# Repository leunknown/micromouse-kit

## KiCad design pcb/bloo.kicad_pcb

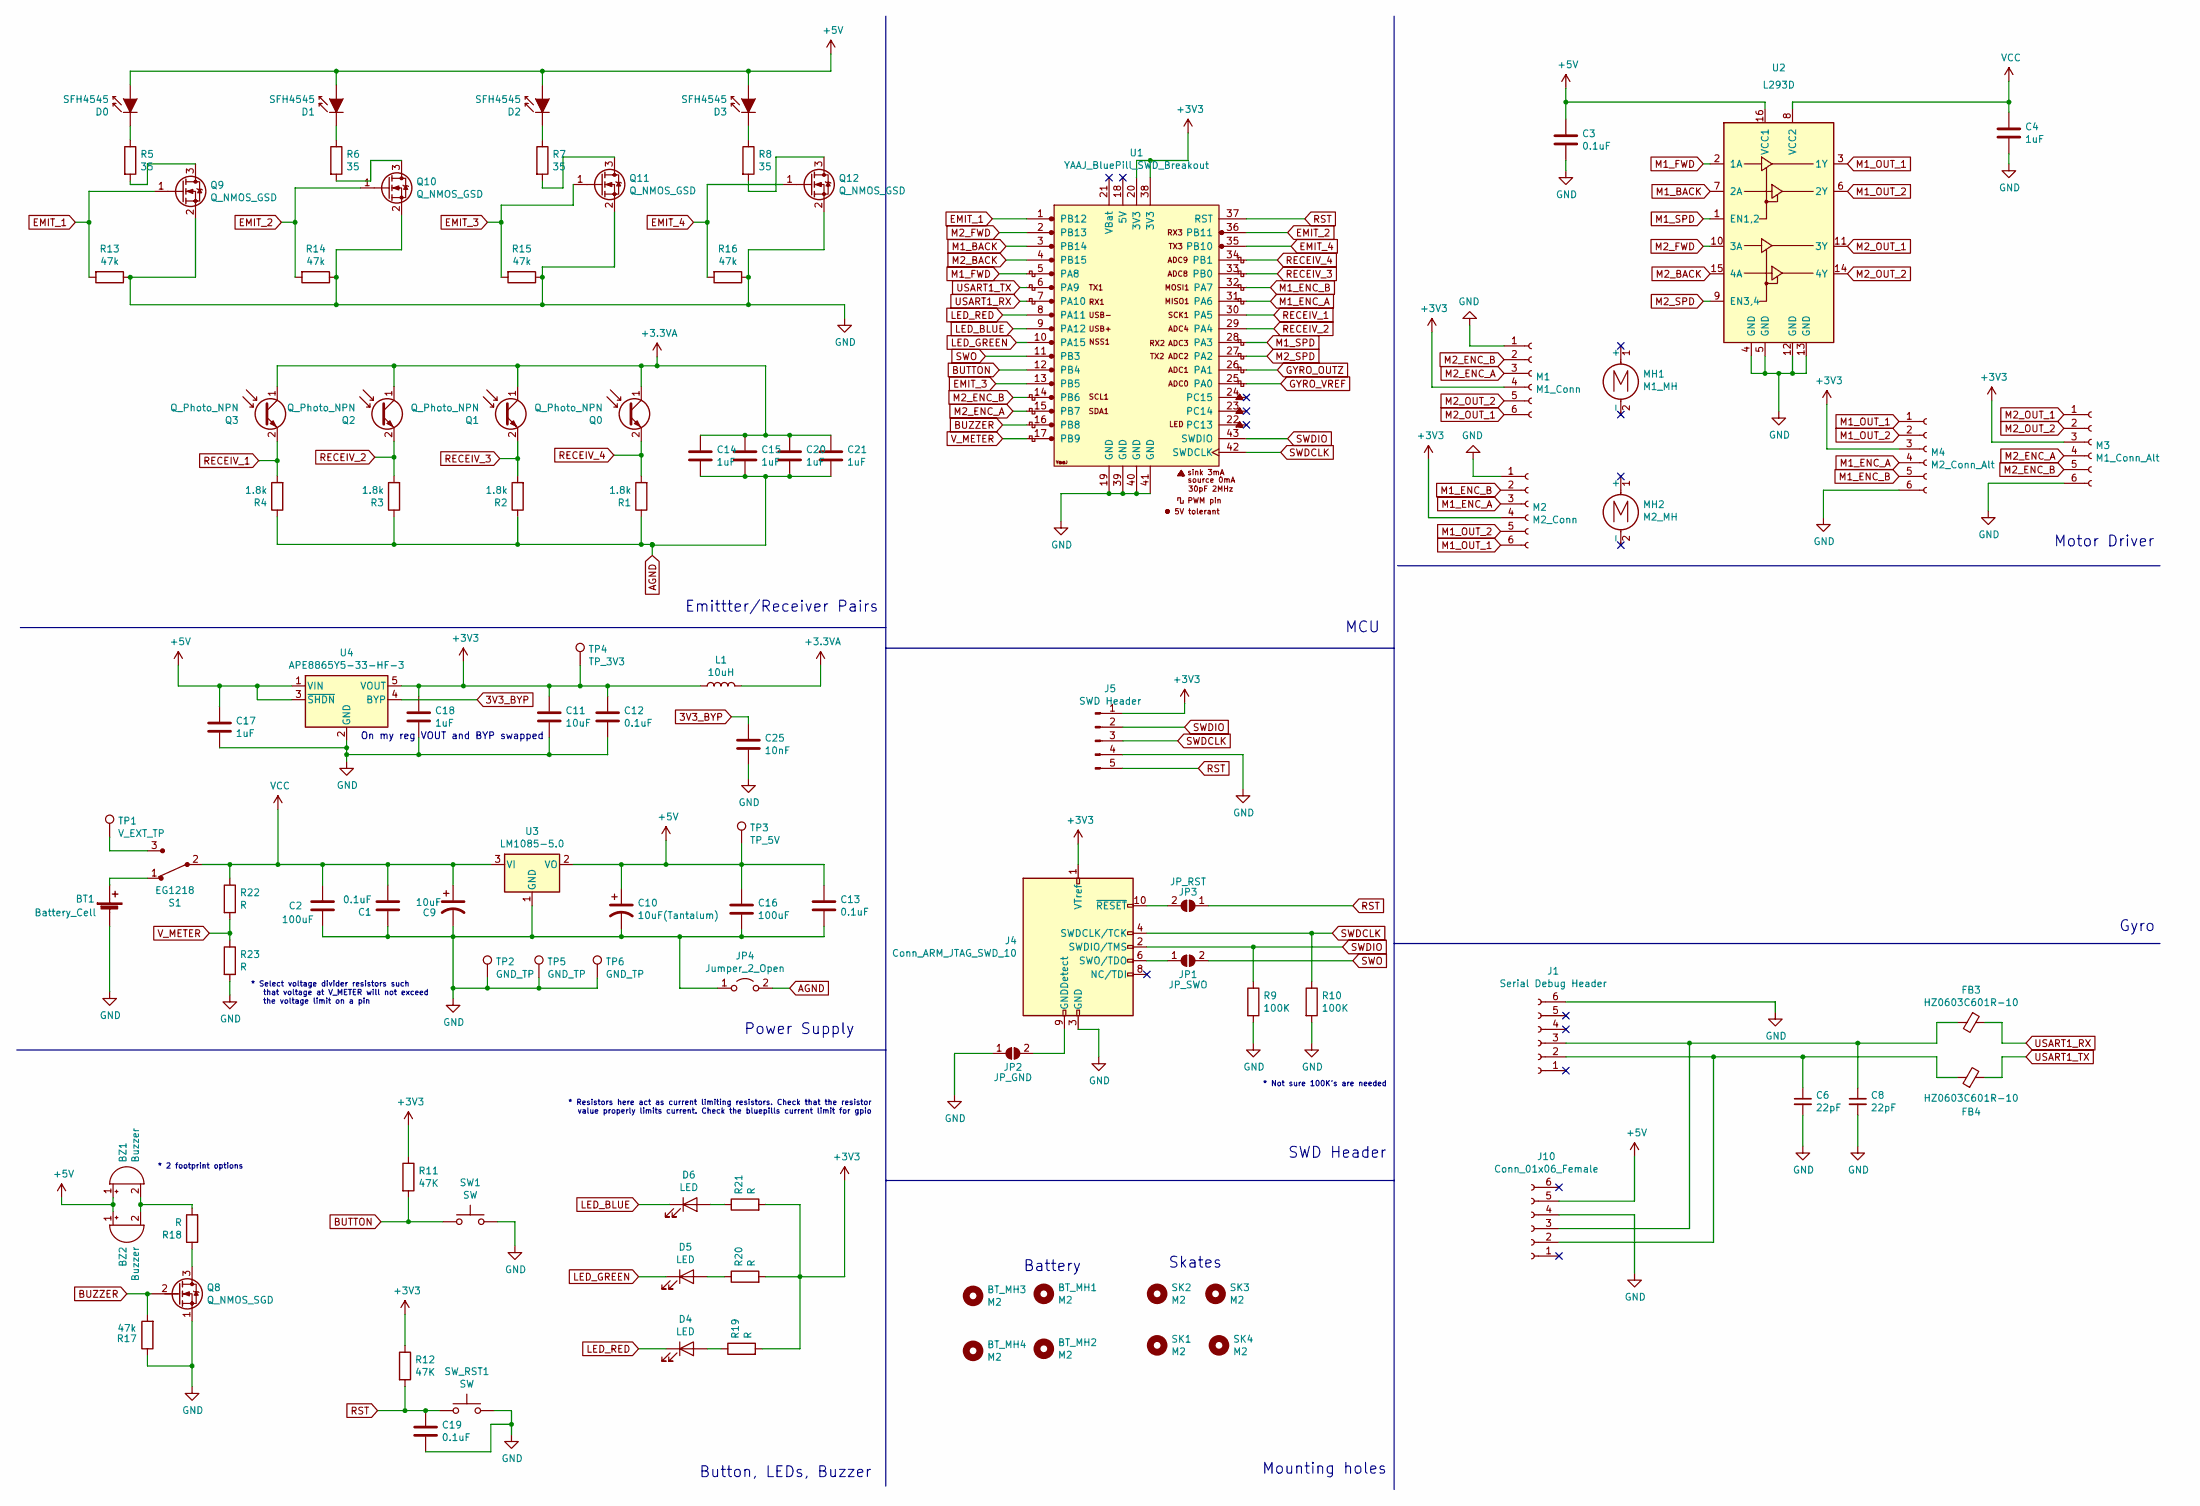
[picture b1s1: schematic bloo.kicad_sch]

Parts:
BT1: Battery_Cell; PinSocket_1x02_P2.54mm_Vertical
BT_MH1, BT_MH2, BT_MH3, BT_MH4: M2; MountingHole_2.2mm_M2
BZ1: Buzzer; Buzzer_12x9.5RM7.6
BZ2: Buzzer; Buzzer_TDK_PS1240P02BT_D12.2mm_H6.5mm
C1, C3, C12, C13, C19: 0.1uF; C_1206_3216Metric_Pad1.33x1.80mm_HandSolder
C2, C16: 100uF; CP_Radial_D6.3mm_P2.50mm
C4, C14, C15, C17, C18, C20, C21: 1uF; C_1206_3216Metric_Pad1.33x1.80mm_HandSolder
C6, C8: 22pF; C_0603_1608Metric_Pad1.08x0.95mm_HandSolder
C9, C11: 10uF; C_1206_3216Metric_Pad1.33x1.80mm_HandSolder
C10: 10uF(Tantalum); C_1206_3216Metric_Pad1.33x1.80mm_HandSolder
C25: 10nF; C_1206_3216Metric_Pad1.33x1.80mm_HandSolder
D0, D1, D2, D3: SFH4545; Emitter
D4, D5, D6: LED; LED_0805_2012Metric_Pad1.15x1.40mm_HandSolder
FB3, FB4: HZ0603C601R-10; R_0603_1608Metric_Pad0.98x0.95mm_HandSolder
J1: Serial Debug Header; PinHeader_1x06_P2.54mm_Vertical
J4: Conn_ARM_JTAG_SWD_10; PinHeader_2x05_P1.27mm_Vertical
J5: SWD Header; PinHeader_1x05_P2.54mm_Vertical
J10: Conn_01x06_Female; PinSocket_1x06_P2.54mm_Vertical
JP1: JP_SWO; SolderJumper-2_P1.3mm_Open_Pad1.0x1.5mm
JP2: JP_GND; SolderJumper-2_P1.3mm_Open_Pad1.0x1.5mm
JP3: JP_RST; SolderJumper-2_P1.3mm_Open_Pad1.0x1.5mm
JP4: Jumper_2_Open; SolderJumper-2_P1.3mm_Bridged_Pad1.0x1.5mm
L1: 10uH; L_1206_3216Metric_Pad1.42x1.75mm_HandSolder
M1: M1_Conn; JST_SH_BM06B-SRSS-TB_1x06-1MP_P1.00mm_Vertical
M2: M2_Conn; JST_SH_BM06B-SRSS-TB_1x06-1MP_P1.00mm_Vertical
M3: M1_Conn_Alt; PinHeader_1x06_P2.54mm_Vertical
M4: M2_Conn_Alt; PinHeader_1x06_P2.54mm_Vertical
MH1: M1_MH; Motor_mouse
MH2: M2_MH; Motor_mouse
Q0, Q1, Q2, Q3: Q_Photo_NPN; Emitter
Q8: Q_NMOS_SGD; SOT-23
Q9, Q10, Q11, Q12: Q_NMOS_GSD; SOT-23
R1, R2, R3, R4: 1.8k; R_1206_3216Metric_Pad1.30x1.75mm_HandSolder
R5, R6, R7, R8: 35; R_1206_3216Metric_Pad1.30x1.75mm_HandSolder
R9, R10: 100K; R_1206_3216Metric_Pad1.30x1.75mm_HandSolder
R11, R12: 47K; R_1206_3216Metric_Pad1.30x1.75mm_HandSolder
R13, R14, R15, R16, R17: 47k; R_1206_3216Metric_Pad1.30x1.75mm_HandSolder
R18, R19, R20, R21, R22, R23: R; R_1206_3216Metric_Pad1.30x1.75mm_HandSolder
S1: EG1218; 1103M2S4CQE2; MPN EG1218; Digi-Key_PN EG1903-ND
SK1, SK2, SK3, SK4: M2; MountingHole_2.2mm_M2
SW1: SW; SW_SPST_REED_CT05-XXXX-G1
SW_RST1: SW; SW_SPST_REED_CT05-XXXX-G1
TP1: V_EXT_TP; PinHeader_1x01_P2.54mm_Vertical
TP2, TP5, TP6: GND_TP; PinHeader_1x01_P2.54mm_Vertical
TP3: TP_5V; PinHeader_1x01_P2.54mm_Vertical
TP4: TP_3V3; PinHeader_1x01_P2.54mm_Vertical
U1: YAAJ_BluePill_SWD_Breakout; YAAJ_BluePill_SWD_2
U2: L293D; DIP-16_W7.62mm
U3: LM1085-5.0; VREG_TO-263-3_TabPin2
U4: APE8865Y5-33-HF-3; SOT-23-5

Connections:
3V3_BYP: C25.1, U4.4 (BYP)
+3.3VA: C14.1, C15.1, C20.1, C21.1, L1.2, Q0.1 (C), Q1.1 (C), Q2.1 (C), Q3.1 (C)
+3V3: C11.1, C12.1, C18.1, J4.1 (VTref), J5.1, L1.1, M1.4, M2.4, M3.3, M4.3, R11.1, R12.1, R19.2, R20.2, R21.2, TP4.1, U1.20 (3V3), U1.38 (3V3), U4.5 (VOUT); also elsewhere on the board
+5V: BZ1.1 (-), BZ2.1 (-), C3.1, C10.1, C13.1, C16.1, C17.1, D0.2 (A), D1.2 (A), D2.2 (A), D3.2 (A), J10.5, TP3.1, U2.16 (VCC1), U3.2 (VO), U4.1 (VIN), U4.3 (~SHDN); also elsewhere on the board
AGND: C14.2, C15.2, C20.2, C21.2, JP4.2 (B), R1.1, R2.1, R3.1, R4.1
BUTTON: R11.2, SW1.1, U1.12 (PB4)
BUZZER: Q8.2 (G), R17.2, U1.16 (PB8)
EMIT_1: Q9.1 (G), R13.2, U1.1 (PB12)
EMIT_2: Q10.1 (G), R14.2, U1.36 (PB11)
EMIT_3: Q11.1 (G), R15.2, U1.13 (PB5)
EMIT_4: Q12.1 (G), R16.2, U1.35 (PB10)
GND: BT1.2 (-), C1.1, C2.2, C3.2, C4.2, C6.2, C8.2, C9.2, C10.2, C11.2, C12.2, C13.2, C16.2, C17.2, C18.2, C19.2, C25.2, J1.6, J4.3 (GND), J4.5 (GND), J5.4, J10.4, JP2.1 (A), JP4.1 (A), M1.1, M2.1, M3.6, M4.6, Q8.1 (S), Q9.2 (S), Q10.2 (S), Q11.2 (S), Q12.2 (S), R9.2, R10.2, R13.1, R14.1, R15.1, R16.1, R17.1, R23.2, SW1.2, SW_RST1.2, TP2.1, TP5.1, TP6.1, U1.19 (GND), U1.39 (GND), U1.40 (GND), U1.41 (GND), U2.4 (GND), U2.5 (GND), U2.12 (GND), U2.13 (GND), U3.1 (GND), U4.2 (GND); also elsewhere on the board
GYRO_OUTZ: U1.26 (PA1)
GYRO_VREF: U1.25 (PA0)
LED_BLUE: D6.1 (K), U1.9 (PA12)
LED_GREEN: D5.1 (K), U1.10 (PA15)
LED_RED: D4.1 (K), U1.8 (PA11)
M1_BACK: U1.3 (PB14), U2.7 (2A)
M1_ENC_A: M2.3, M4.4, U1.31 (PA6)
M1_ENC_B: M2.2, M4.5, U1.32 (PA7)
M1_FWD: U1.5 (PA8), U2.2 (1A)
M1_OUT_1: M2.6, M4.1, U2.3 (1Y)
M1_OUT_2: M2.5, M4.2, U2.6 (2Y)
M1_SPD: U1.28 (PA3), U2.1 (EN1,2)
M2_BACK: U1.4 (PB15), U2.15 (4A)
M2_ENC_A: M1.3, M3.4, U1.15 (PB7)
M2_ENC_B: M1.2, M3.5, U1.14 (PB6)
M2_FWD: U1.2 (PB13), U2.10 (3A)
M2_OUT_1: M1.6, M3.1, U2.11 (3Y)
M2_OUT_2: M1.5, M3.2, U2.14 (4Y)
M2_SPD: U1.27 (PA2), U2.9 (EN3,4)
unnamed: BT1.1 (+), S1.1
unnamed: BZ1.2 (+), BZ2.2 (+), R18.2
unnamed 34: C6.1, FB4.1, J1.2, J10.2; also elsewhere on the board
unnamed 35: C8.1, FB3.2, J1.3, J10.3; also elsewhere on the board
unnamed: D0.1 (K), R5.1
unnamed: D1.1 (K), R6.1
unnamed: D2.1 (K), R7.1
unnamed: D3.1 (K), R8.1
unnamed: D4.2 (A), R19.1
unnamed: D5.2 (A), R20.1
unnamed: D6.2 (A), R21.1
unnamed: J4.6 (SWO/TDO), JP1.1 (A)
unnamed: J4.9 (GNDDetect), JP2.2 (B)
unnamed: J4.10 (~RESET), JP3.2 (B)
unnamed: Q8.3 (D), R18.1
unnamed: Q9.3 (D), R5.2
unnamed: Q10.3 (D), R6.2
unnamed: Q11.3 (D), R7.2
unnamed: Q12.3 (D), R8.2
unnamed: S1.3, TP1.1
RECEIV_1: Q3.2 (E), R4.2, U1.30 (PA5)
RECEIV_2: Q2.2 (E), R3.2, U1.29 (PA4)
RECEIV_3: Q1.2 (E), R2.2, U1.33 (PB0)
RECEIV_4: Q0.2 (E), R1.2, U1.34 (PB1)
RST: C19.1, J5.5, JP3.1 (A), R12.2, SW_RST1.1, U1.37 (RST); also elsewhere on the board
SWDCLK: J4.4 (SWDCLK/TCK), J5.3, R10.1, U1.42 (SWDCLK)
SWDIO: J4.2 (SWDIO/TMS), J5.2, R9.1, U1.43 (SWDIO)
SWO: JP1.2 (B), U1.11 (PB3)
USART1_RX: FB3.1, U1.7 (PA10)
USART1_TX: FB4.2, U1.6 (PA9)
VCC: C1.2, C2.1, C4.1, C9.1, R22.1, S1.2, U2.8 (VCC2), U3.3 (VI)
V_METER: R22.2, R23.1, U1.17 (PB9)

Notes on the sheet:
Mounting holes
Battery
* 2 footprint options
Motor Driver
* Not sure 100K’s are needed
On my reg VOUT and BYP swapped
Emittter/Receiver Pairs
* Resistors here act as current limiting resistors. Check that the resistor value properly limits current. Check the bluepills current limit for gpio
MCU
SWD Header
* Select voltage divider resistors such that voltage at V_METER will not exceed the voltage limit on a pin
Gyro
Button, LEDs, Buzzer
Skates
Power Supply

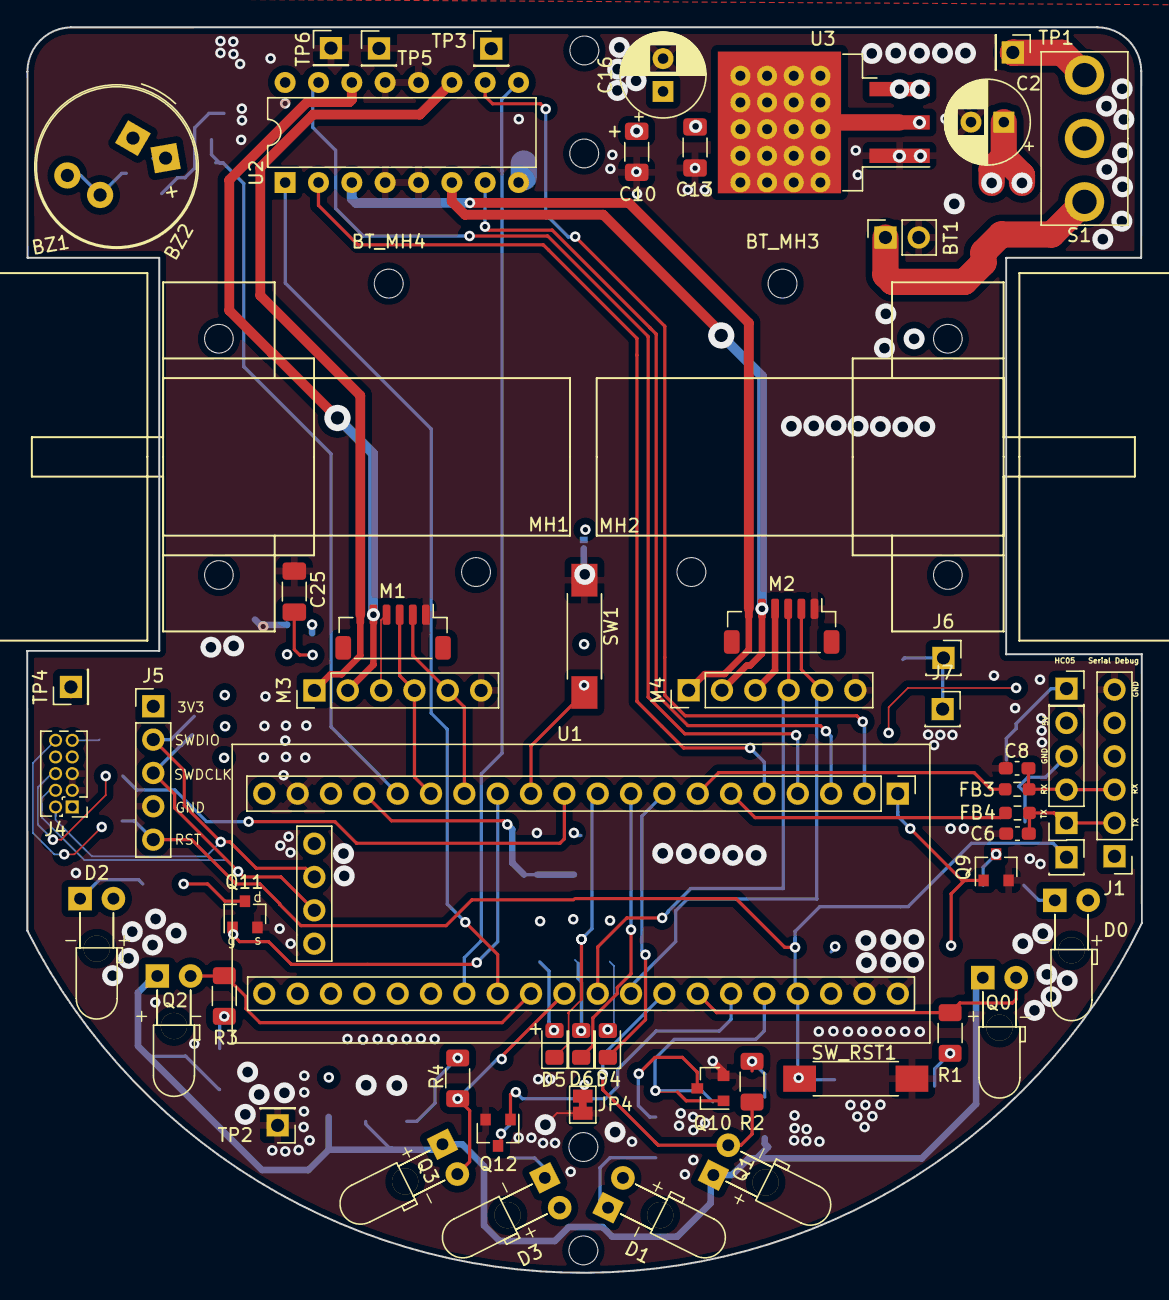
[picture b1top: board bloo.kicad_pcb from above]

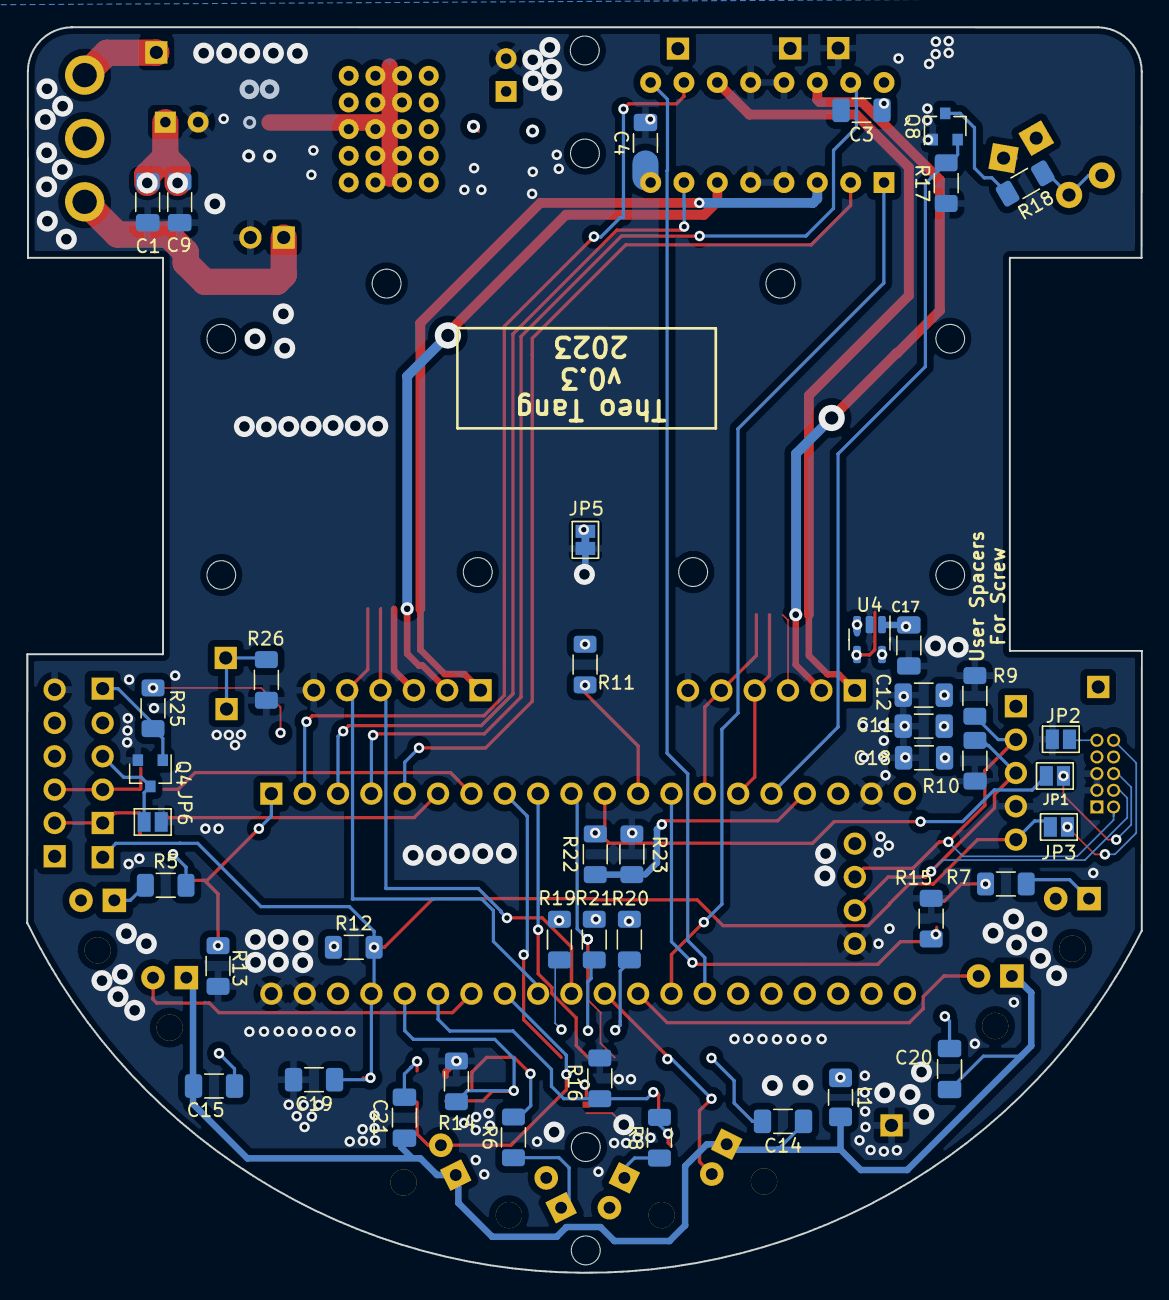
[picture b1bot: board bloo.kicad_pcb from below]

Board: 4 copper layers, 84.9 x 94.9 mm, 109 parts (43 on the bottom side), 64 nets.

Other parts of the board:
J2: Conn_RST; PinSocket_1x01_P2.54mm_Vertical
J3: BLE_PWR; PinSocket_1x01_P2.54mm_Vertical
J6, J7: BOOT0; PinSocket_1x01_P2.54mm_Vertical
J8: Conn_01x04_Female; PinSocket_1x04_P2.54mm_Vertical
JP5: Jumper_2_Open; SolderJumper-2_P1.3mm_Bridged_Pad1.0x1.5mm
JP6: Jumper_2_Open; SolderJumper-2_P1.3mm_Open_Pad1.0x1.5mm
Q4: Q_NMOS_GSD; SOT-23
R25, R26: 47k; R_1206_3216Metric_Pad1.30x1.75mm_HandSolder

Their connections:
+3V3: R25.1; also elsewhere on the board
+5V: J8.4; also elsewhere on the board
GND: JP5.1, JP6.2, Q4.2, R26.1; also elsewhere on the board
unnamed 34: J8.1; also elsewhere on the board
unnamed 35: J8.2; also elsewhere on the board
unnamed: J3.1, Q4.1, R25.2
unnamed: J6.1, J7.1, R26.2
unnamed: J8.3, JP6.1, Q4.3
RST: J2.1; also elsewhere on the board

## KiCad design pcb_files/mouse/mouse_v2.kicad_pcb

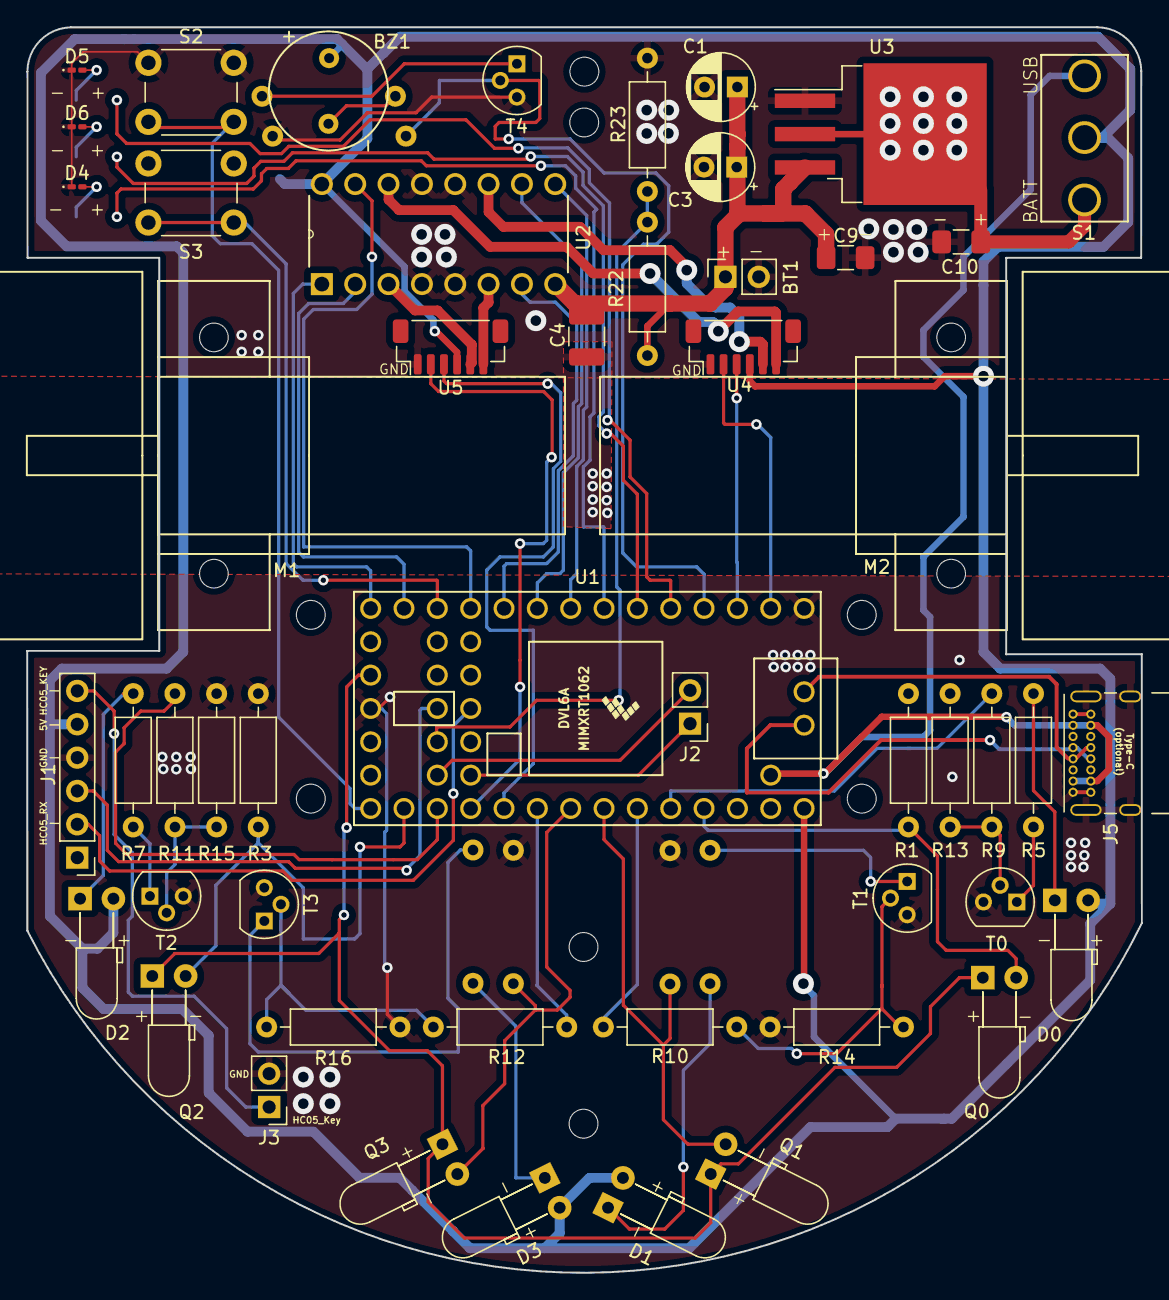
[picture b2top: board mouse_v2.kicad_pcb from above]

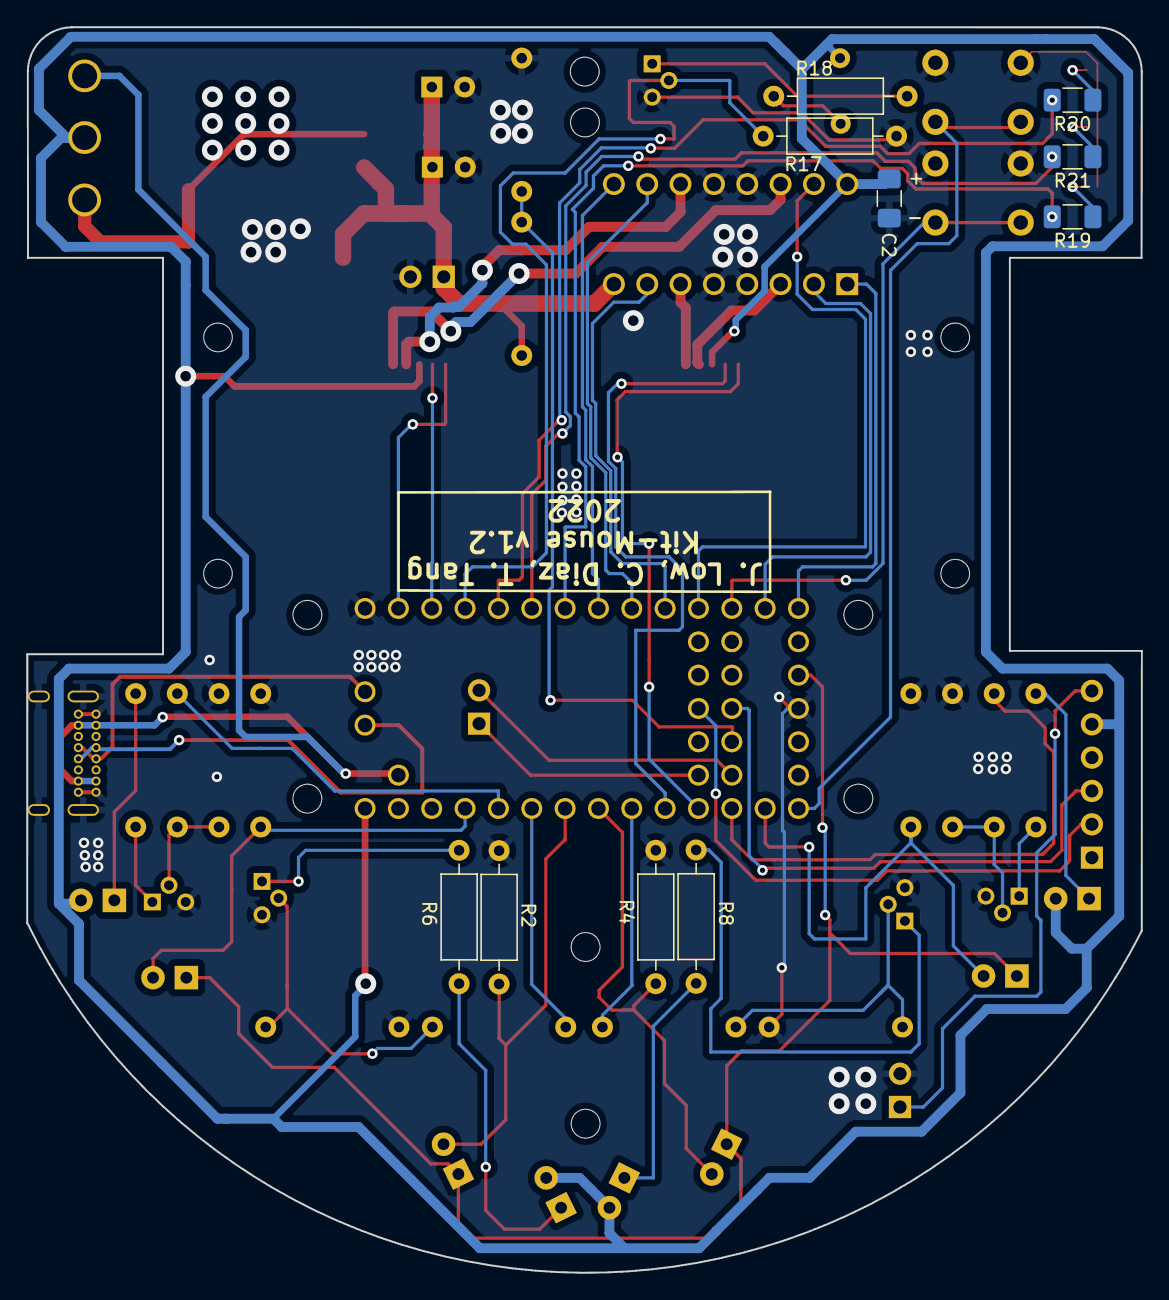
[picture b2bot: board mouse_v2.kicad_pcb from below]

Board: 2 copper layers, 84.9 x 94.9 mm, 69 parts (10 on the bottom side), 59 nets.

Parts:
BT1: Battery_Cell; PinSocket_1x02_P2.54mm_Vertical
BZ1: Buzzer; 9x5.5mm Buzzer
C1, C3: 100uF; CP_Radial_D5.0mm_P2.50mm
C2: 0.1uF; C_1206_3216Metric_Pad1.42x1.75mm_HandSolder
C4: 1uF; C_1210_3225Metric_Pad1.33x2.70mm_HandSolder
C9: 10uF; C_1206_3216Metric_Pad1.42x1.75mm_HandSolder
C10: 10uF(Tantalum); C_1206_3216Metric_Pad1.42x1.75mm_HandSolder
D0, D1, D2, D3: SFH4545; LED_D3.0mm_Horizontal_O3.81mm_Z2.0mm
D4, D5, D6: LED; LED_0201_0603Metric_Pad0.64x0.40mm_HandSolder
J1: Conn_01x06_Female; PinHeader_1x06_P2.54mm_Vertical
J2: Conn_01x02_Female; PinHeader_1x02_P2.54mm_Vertical
J3: Conn_01x02_Male; PinHeader_1x02_P2.54mm_Vertical
J5: USB_C_Receptacle_USB2.0; USB_C_Receptacle_GCT_USB4085
M1, M2: Motor_DC; Motor_mouse
MH1, MH2, MH3, MH4: M3; MountingHole_2.2mm_M2
Q0, Q1, Q2, Q3: Q_Photo_NPN; LED_D3.0mm_Horizontal_O3.81mm_Z2.0mm
R1, R2, R3, R4: 1.8k; R_Axial_DIN0207_L6.3mm_D2.5mm_P10.16mm_Horizontal
R5, R6, R7, R8: 35; R_Axial_DIN0207_L6.3mm_D2.5mm_P10.16mm_Horizontal
R9, R10, R11, R12: 1k; R_Axial_DIN0207_L6.3mm_D2.5mm_P10.16mm_Horizontal
R13, R14, R15, R16, R17: 47k; R_Axial_DIN0207_L6.3mm_D2.5mm_P10.16mm_Horizontal
R18, R22, R23: R; R_Axial_DIN0207_L6.3mm_D2.5mm_P10.16mm_Horizontal
R19, R20, R21: R; R_1206_3216Metric_Pad1.30x1.75mm_HandSolder
S1: EG1218; SWITCH_SLIDE_500SSP1S2M2QEA
S2, S3: GPTS203211B; SW_PUSH_6mm
SK1, SK2, SK3, SK4: M3; MountingHole_2.2mm_M2
T0, T1, T2, T3, T4: Q_NMOS_DGS; TN0104(TO-92)v2
U1: Teensy4.0; Teensy40
U2: SN754410NE (Half-Bridge); DIP254P762X508-16
U3: LM1085-5.0; TO-263-3_TabPin2
U4, U5: Encoder_3081; JST_SH_BM06B-SRSS-TB_1x06-1MP_P1.00mm_Vertical

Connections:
/3.3v: Q0.1 (C), Q1.1 (C), Q2.1 (C), Q3.1 (C), U1.16 (3V3)
/5v: BZ1.1 (-), C2.1, D0.2 (A), D1.2 (A), D2.2 (A), D3.2 (A), J1.5, S1.2, U1.33 (VIN), U2.16 (VCC1), U4.4 (VCC), U5.4 (VCC)
/Buzzer: R17.2, T4.2 (G), U1.4 (2_OUT2)
/D+: J5.A6 (D+), J5.B6 (D+), U1.54 (D+)
/D-: J5.A7 (D-), J5.B7 (D-), U1.53 (D-)
/Emitter_0: R9.2, U1.29 (22_A8_CTX1)
/Emitter_1: R10.2, U1.28 (21_A7_RX5_BCLK1)
/Emitter_2: R11.2, U1.22 (15_A1_RX3_SPDIF_IN)
/Emitter_3: R12.2, U1.25 (18_A4_SDA0)
/GND: BT1.2 (-), C1.2, C2.2, C3.2, C4.2, C9.2, C10.2, D4.1 (K), D5.1 (K), D6.1 (K), J1.4, J3.2, J5.A1 (GND), J5.A12 (GND), J5.B1 (GND), J5.B12 (GND), J5.S1 (SHIELD), R1.1, R2.1, R3.1, R4.1, R13.1, R14.1, R15.1, R16.1, R17.1, R23.2, S2.1, S3.1, T0.3 (S), T1.3 (S), T2.3 (S), T3.3 (S), T4.3 (S), U1.1 (GND), U1.17 (GND), U2.4 (GND_3), U2.5 (GND_4), U2.12 (GND), U2.13 (GND_2), U3.1 (GND), U4.1 (GND), U5.1 (GND)
/HC05_KEY: J1.6, J3.1
/HC05_RX: J1.2, U1.40 (29_TX7)
/HC05_TX: J1.3, U1.39 (28_RX7)
/LED_1: R19.2, U1.7 (5_IN2)
/LED_2: R20.2, U1.5 (3_LRCLK2)
/LED_3: R21.2, U1.6 (4_BCLK2)
/M1_backward: U1.10 (8_TX2_IN1), U2.7 (2A)
/M1_encoder_A: U1.24 (17_A3_TX4_SDA1), U5.3 (A)
/M1_encoder_B: U1.23 (16_A2_RX4_SCL1), U5.2 (B)
/M1_forward: U1.13 (11_MOSI_CTX1), U2.2 (1A)
/M1_speed: U1.14 (12_MISO_MQSL), U2.1 (1,2EN)
/M2_backward: U1.11 (9_OUT1C), U2.15 (4A)
/M2_encoder_A: U1.3 (1_TX1_CTX2_MISO1), U4.3 (A)
/M2_encoder_B: U1.2 (0_RX1_CRX2_CS1), U4.2 (B)
/M2_forward: U1.9 (7_RX2_OUT1A), U2.10 (3A)
/M2_speed: U1.8 (6_OUT1D), U2.9 (3,4EN)
/OUT1: U2.3 (1Y), U5.5 (M2)
/OUT2: U2.6 (2Y), U5.6 (M1)
/OUT3: U2.11 (3Y), U4.5 (M2)
/OUT4: U2.14 (4Y), U4.6 (M1)
/PUSH_SW: S2.2, U1.20 (13_SCK_CRX1_LED)
/PUSH_SW2: S3.2, U1.12 (10_CS_MQSR)
/Reciever_0: Q0.2 (E), R1.2, U1.30 (23_A9_CRX1_MCLK1)
/Reciever_1: Q1.2 (E), R2.2, U1.27 (20_A6_TX5_LRCLK1)
/Reciever_2: Q2.2 (E), R3.2, U1.21 (14_A0_TX3_SPDIF_OUT)
/Reciever_3: Q3.2 (E), R4.2, U1.26 (19_A5_SCL0)
/SCL2: J2.2, U1.35 (24_A10_TX6_SCL2)
/SDA2: J2.1, U1.36 (25_A11_RX6_SDA2)
/VUSB: J5.A4 (VBUS), J5.A9 (VBUS), J5.B4 (VBUS), J5.B9 (VBUS), S1.3, U1.34 (VUSB)
/V_METER: R22.2, R23.1, U1.37 (26_A12_MOSI1)
/vBatt: BT1.1 (+), C1.1, C3.1, C4.1, C9.1, R22.1, U2.8 (VCC2), U3.3 (VI)
unnamed: BZ1.2 (+), R18.1
unnamed: C10.1, S1.1, U3.2 (VO)
unnamed: D0.1 (K), R5.1
unnamed: D1.1 (K), R6.1
unnamed: D2.1 (K), R7.1
unnamed: D3.1 (K), R8.1
unnamed: D4.2 (A), R19.1
unnamed: D5.2 (A), R20.1
unnamed: D6.2 (A), R21.1
unnamed: R5.2, T0.1 (D)
unnamed: R6.2, T1.1 (D)
unnamed: R7.2, T2.1 (D)
unnamed: R8.2, T3.1 (D)
unnamed: R10.1, R14.2, T1.2 (G)
unnamed: R11.1, R15.2, T2.2 (G)
unnamed: R12.1, R16.2, T3.2 (G)
unnamed: R9.1, R13.2, T0.2 (G)
unnamed: R18.2, T4.1 (D)

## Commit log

2022-06-01 V1.2
2022-06-01 Motor Risers
2022-06-01 Maze + motor mounts
